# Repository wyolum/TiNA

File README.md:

TiNA
====

Standalone controller for TIM (The Intelligent Matrix)

To install arduino libraries:
1. download and unzip (or git clone) the files to a local directory
   for example, my this is /home/justin/code/TiNA
2. set your arduino sketchbook path to the arduino subdirectory of your install path by either 
    a. editing your ~/.arduino/preferences.txt (the sketchbook.path variable)
    b. selecting from the "File->Preferences" drop down menu item
    for example, my sketchbook path is /home/justin/code/TiNA/arduino
3. start or restart the Arduino IDE

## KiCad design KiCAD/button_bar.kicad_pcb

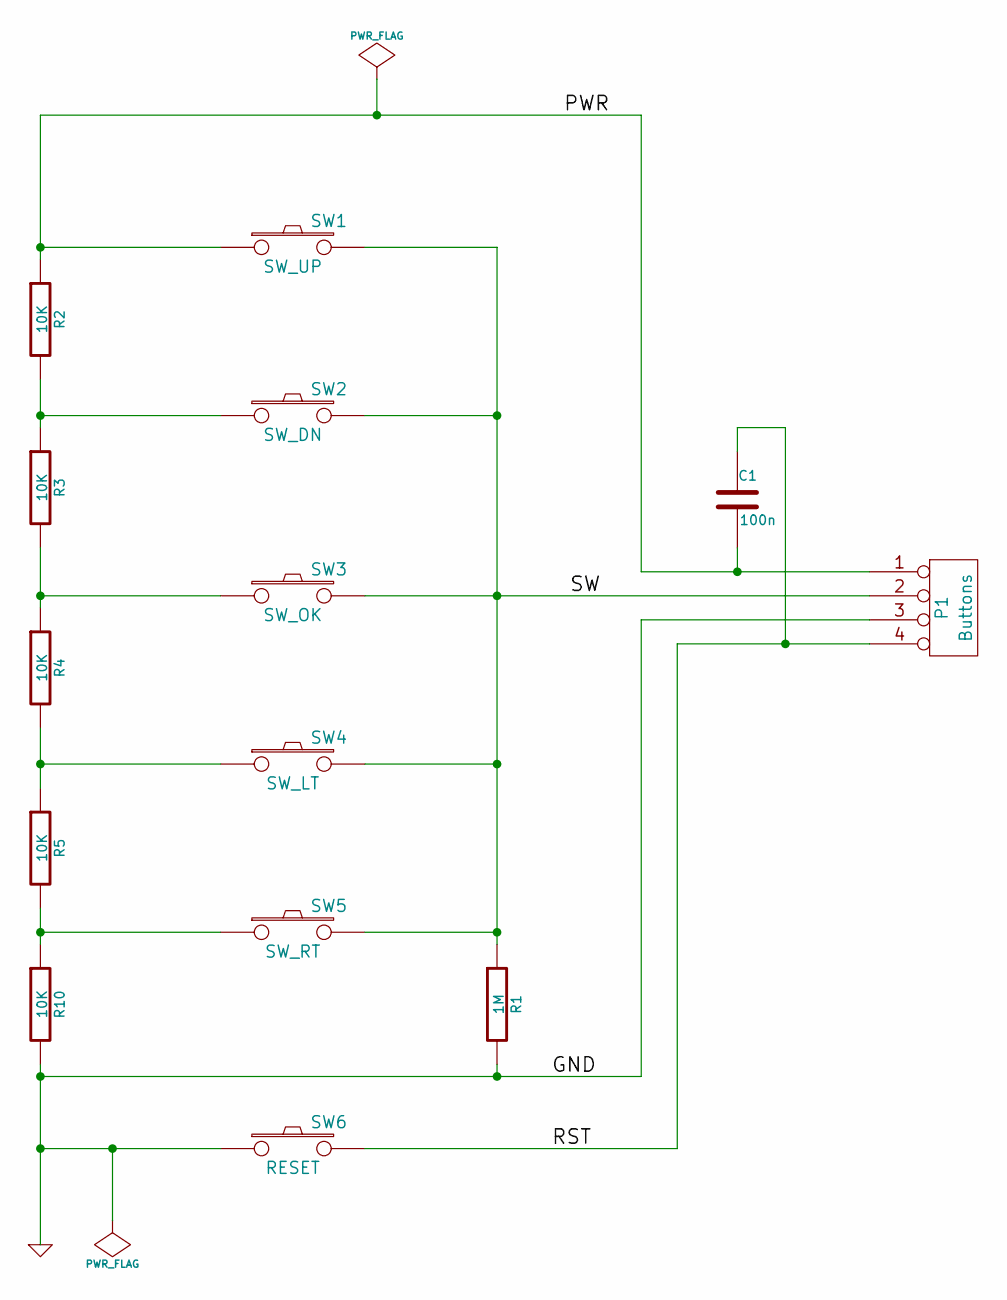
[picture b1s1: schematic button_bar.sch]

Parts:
C1: 100n; C2
P1: Buttons; SIL-4
R1: 1M; RC03
R2, R3, R4, R5, R10: 10K; RC03
SW1: SW_UP; SW-PB
SW2: SW_DN; SW-PB
SW3: SW_OK; SW-PB
SW4: SW_LT; SW-PB
SW5: SW_RT; SW-PB
SW6: RESET; SW-PB

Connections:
/PWR: C1.2, P1.1, R2.1, SW1.1
/RST: C1.1, P1.4, SW6.2
/SW: P1.2, R1.1, SW1.2, SW2.2, SW3.2, SW4.2, SW5.2
GND: P1.3, R1.2, R10.2, SW6.1
unnamed: R5.2, R10.1, SW5.1
unnamed: R4.2, R5.1, SW4.1
unnamed: R3.2, R4.1, SW3.1
unnamed: R2.2, R3.1, SW2.1

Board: 2 copper layers, 14 parts (0 on the bottom side), 8 nets, no tracks yet.

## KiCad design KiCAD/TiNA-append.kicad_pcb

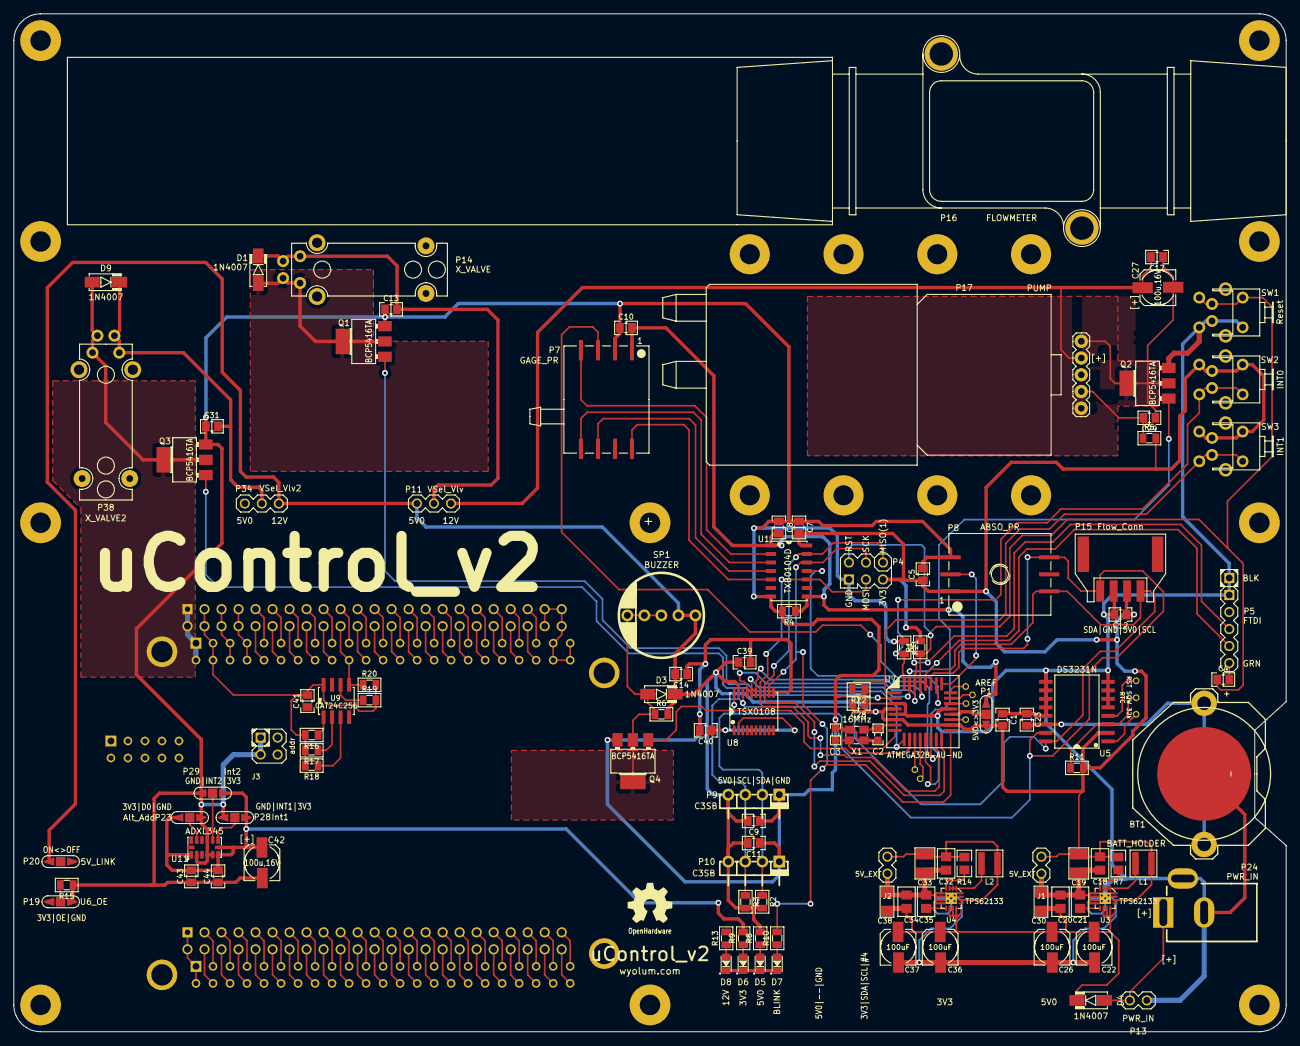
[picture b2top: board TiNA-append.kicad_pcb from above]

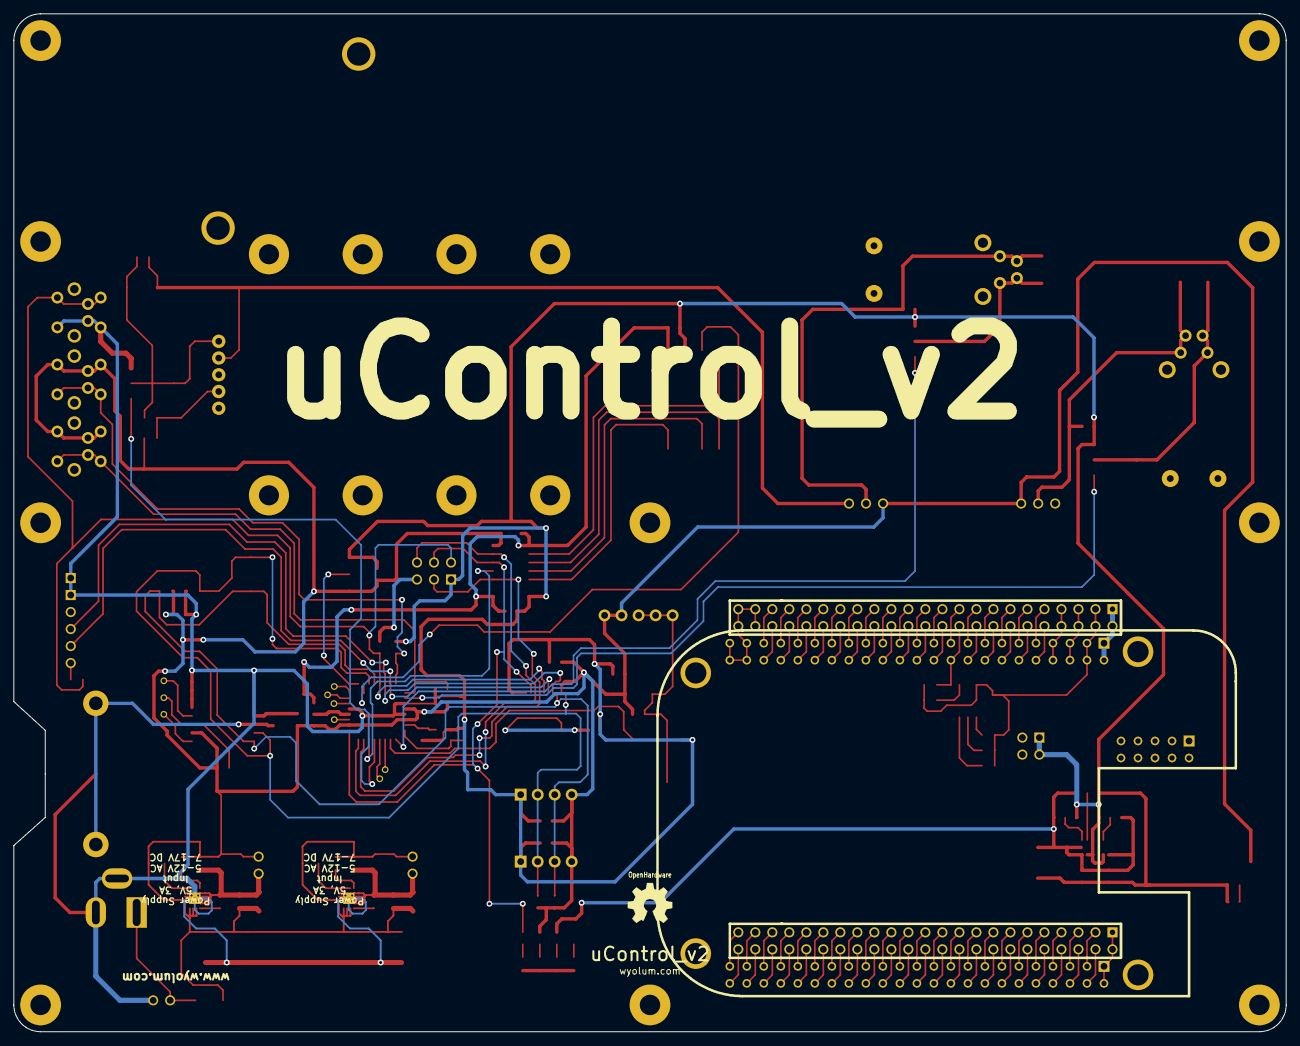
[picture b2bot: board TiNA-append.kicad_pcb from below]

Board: 2 copper layers, 190.0 x 152.0 mm, 137 parts (4 on the bottom side), 147 nets.

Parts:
B1, B2, B3: I_O
B4, B12: PB0; I_O
B8: PC0; I_O
B9: PC1; I_O
B10: PC6; I_O
B11: PC7; I_O
BT1: BATT_HOLDER; CR2032
C1, C4, C5, C7, C8, C9, C10, C11, C12, C13, C14, C17, C23, C28, C29, C31, C39, C40, C41, C43, C44: 100n; c_0805
C2, C3: 22p; c_0603
C18, C20, C32, C34: 100nF; c_0805
C19, C33: 22uF X7R; c_1210
C21, C35: 3.3nF; c_0805
C22, C26, C36, C37: 100uF; C_ELCO_SMD
C27, C42: 100u,16V; C_ELCO_SMD
C30, C38: 10uF X7R; c_1206
D1, D3, D4, D9: 1N4007; diode-DO214AC
D5: 5V0; led_0805
D6: 3V3; led_0805
D7: BLINK; led_0805
D8: 12V; led_0805
G3, G4: Logo_OH; OSHW_6mm
J1, J2: 5V_EXT; Header_2
J3: addr; Header_2x2
L1, L2: 2u2H,3.0A; Inductor_SMD3
P1: AREF; ShortLink2
P4: ICSP; Header_ISP
P5: FTDI; Header_FTDI
P7: GAGE_PR; HCEM500GUH9P3
P8: ABSO_PR; HDIB002AUY8H5
P9, P10: C3SB; pin_strip_4-90
P11: VSel_Vlv; Header_3
P13: PWR_IN; Header_2
P14: X_VALVE; X_Valve_2
P15: Flow_Conn; Conn_Flow_SFM3000_Male
P16: FLOWMETER; FlowMeter_CFM3000
P17: PUMP; Pump_P54E01R_02
P19: U6_OE; ShortLink2
P20: 5V_LINK; ShortLink2
P21, P22: CONN_23X2; PIN_ARRAY_23X2
P23: Alt_Add; ShortLink2
P24: PWR_IN; JACK_ALIM
P28: Int1; ShortLink2
P29: Int2; ShortLink2
P34: VSel_Vlv2; Header_3
P38: X_VALVE2; X_Valve_2
PCB1: PCB
Q1, Q2, Q3, Q4: BCP5416TA; SOT223
R1, R2, R3, R4, R11, R15, R21, R22: 10k; r_0805
R5: 4k7; r_0805
R6, R10, R13: 1k; r_0805
R7, R14: 100k; r_0805
R8: 330E; r_0805
R9: 120E; r_0805
R16, R17, R18: 4k75; r_0805
R19, R20: 1k5; r_0805
SC1, SC2, SC3, SC4, SC5, SC6, SC7, SC8, SC9, SC10: SCREW; vite_3mm
SP1: BUZZER; Speaker
SW1: Reset; SW_PB_V_H
SW2: INT0; SW_PB_V_H
SW3: INT1; SW_PB_V_H
U1: TXB0104D
U3, U4: TPS62133; TPS62132
U5: DS3231N; DS3231
U7: ATMEGA328-AU-ND; TQFP32
U8: TSX0108; TXS0108EPWR
U9: CAT24C256; SO8E
U10: BEAGLEBONE
U11: ADXL345
X1: 16MHz; Xtal_SMD3

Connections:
+3.3V: C8.1, C10.1, C32.2, C33.1, C42.1, C43.1, C44.1, J2.1, L2.2, P1.1, P7.1, P23.3, P28.3, P29.3, R4.2, R9.1, R14.2, U1.1, U1.8, U4.14, U11.1, U11.6, U11.7
/AREF: P1.2, U7.20
/BBB/5V0: C1.1, C5.2, C7.1, C9.1, C11.1, C12.2, C14.1, C18.2, C19.1, C28.1, C39.2, D3.2, J1.1, L1.2, P1.3, P4.2, P8.1, P9.1, P10.1, P11.1, P15.2, P20.1, P34.1, R1.1, R2.1, R3.1, R5.1, R6.1, R7.2, R8.1, R11.1, SP1.1, SW2.2, SW3.2, U1.14, U3.14, U5.2, U7.4, U7.6, U7.18, U8.19
/BBB/A0: J3.3, R16.2, U9.1
/BBB/A1: J3.1, R17.2, U9.2
/BBB/A2: R18.2, U9.3
/BBB/ACL_INT1: P28.2, U11.8
/BBB/ACL_INT2: P29.2, U11.9
/BBB/ACL_SDO: P23.2, U11.12
/BBB/AIN0: P21.39, U10.C39
/BBB/AIN1: P21.40, U10.C40
/BBB/AIN2: P21.37, U10.C37
/BBB/AIN3: P21.38, U10.C38
/BBB/AIN4: P21.33, U10.C33
/BBB/AIN5: P21.36, U10.C36
/BBB/AIN6: P21.35, U10.C35
/BBB/BBB_OE: P19.2, R15.1, U8.10
/BBB/CLKOUT2: P21.41, U10.C41
/BBB/DGND_8: P22.1, P22.2, U10.B1, U10.B2
/BBB/DGND_9_2: P21.43, P21.44, P21.45, P21.46, U10.C43, U10.C44, U10.C45, U10.C46
/BBB/EHRPWM1A: P21.14, U10.C14
/BBB/EHRPWM1B: P21.16, U10.C16
/BBB/EHRPWM2A: P22.19, U10.B19
/BBB/EHRPWM2B: P22.13, U10.B13
/BBB/GNDA_ADC: P21.34, U10.C34
/BBB/GPIO0_7: P21.42, U10.C42
/BBB/GPIO0_26: P22.14, U10.B14
/BBB/GPIO0_27: P22.17, U10.B17
/BBB/GPIO1_0: P22.25, U10.B25
/BBB/GPIO1_1: P22.24, U10.B24
/BBB/GPIO1_2: P22.5, U10.B5
/BBB/GPIO1_3: P22.6, U10.B6
/BBB/GPIO1_4: P22.23, U10.B23
/BBB/GPIO1_5: P22.22, U10.B22
/BBB/GPIO1_6: P22.3, U10.B3
/BBB/GPIO1_7: P22.4, U10.B4
/BBB/GPIO1_12: P22.12, U10.B12
/BBB/GPIO1_13: P22.11, U10.B11
/BBB/GPIO1_14: P22.16, U10.B16
/BBB/GPIO1_15: P22.15, U10.B15
/BBB/GPIO1_16: P21.15, U10.C15
/BBB/GPIO1_17: P21.23, U10.C23
/BBB/GPIO1_28: P21.12, U10.C12
/BBB/GPIO1_29: P22.26, U10.B26
/BBB/GPIO1_30: P22.21, U10.B21
/BBB/GPIO1_31: P22.20, U10.B20
/BBB/GPIO2_1: P22.18, U10.B18
/BBB/GPIO2_6: P22.45, U10.B45
/BBB/GPIO2_7: P22.46, U10.B46
/BBB/GPIO2_8: P22.43, U10.B43
/BBB/GPIO2_9: P22.44, U10.B44
/BBB/GPIO2_10: P22.41, U10.B41
/BBB/GPIO2_11: P22.42, U10.B42
/BBB/GPIO2_13: P22.40, U10.B40
/BBB/GPIO2_22: P22.27, U10.B27
/BBB/GPIO2_23: P22.29, U10.B29
/BBB/GPIO2_24: P22.28, U10.B28
/BBB/GPIO2_25: P22.30, U10.B30
/BBB/GPIO3_19: P21.27, U10.C27
/BBB/GPIO3_21: P21.25, U10.C25
/BBB/GPIO_12: P22.39, U10.B39
/BBB/I2C1_SCL: P21.17, U8.3, U10.C17, U11.14
/BBB/I2C1_SDA: P21.18, U8.1, U10.C18, U11.13
/BBB/I2C2_SCL: P21.19, R19.2, U9.6, U10.C19
/BBB/I2C2_SDA: P21.20, R20.2, U9.5, U10.C20
/BBB/MISO: P4.1, U1.13, U7.16, U8.13
/BBB/PWR_BUT: P21.9, U10.C9
/BBB/RESET: C4.2, P4.5, R1.2, SW1.2, U7.29, U8.15
/BBB/RXD: P5.4, U7.30, U8.17
/BBB/SCK: P4.3, R10.1, U1.12, U7.17, U8.12
/BBB/SCL: P8.6, P9.2, P10.2, P15.1, R3.2, U5.16, U7.28, U8.18
/BBB/SDA: P8.4, P9.3, P10.3, P15.4, R2.2, U5.15, U7.27, U8.20
/BBB/SPI1_CS0: P21.28, U10.C28
/BBB/SPI1_D0: P21.29, U8.8, U10.C29
/BBB/SPI1_D1: P21.30, U8.7, U10.C30
/BBB/SPI1_SCLK: P21.31, U8.9, U10.C31
/BBB/SYS_5V: P21.7, P21.8, U10.C7, U10.C8
/BBB/SYS_RESETn: P21.10, U10.C10
/BBB/TIMER4: P22.7, U10.B7
/BBB/TIMER5: P22.9, U10.B9
/BBB/TIMER6: P22.10, U10.B10
/BBB/TIMER7: P22.8, U10.B8
/BBB/TXD: P5.5, U7.31, U8.16
/BBB/UART1_RXD: P21.26, U8.5, U10.C26
/BBB/UART1_TXD: P21.24, U8.4, U10.C24
/BBB/UART2_RXD: P21.22, U10.C22
/BBB/UART2_TXD: P21.21, U10.C21
/BBB/UART3_CTSN: P22.36, U10.B36
/BBB/UART3_RTSN: P22.34, U10.B34
/BBB/UART4_CTSN: P22.35, U10.B35
/BBB/UART4_RTSN: P22.33, U10.B33
/BBB/UART4_RXD: P21.11, U10.C11
/BBB/UART4_TXD: P21.13, U10.C13
/BBB/UART5_CTSN: P22.31, U10.B31
/BBB/UART5_RTSN: P22.32, U10.B32
/BBB/UART5_RXD: P22.38, U10.B38
/BBB/UART5_TXD: P22.37, U10.B37
/BBB/VDD_3V3EXP: C40.2, C41.1, P19.1, P21.3, P21.4, R16.1, R17.1, R18.1, R19.1, R20.1, U8.2, U9.8, U10.C3, U10.C4
/BBB/VDD_5V: P20.2, P21.5, P21.6, U10.C5, U10.C6
/BBB/VDD_ADC: P21.32, U10.C32
/BBB/~MOSI: P4.4, U1.10, U7.15, U8.14
/Interface/12V: C17.1, C20.2, C22.1, C26.1, C27.1, C30.1, C34.2, C36.1, C37.1, C38.1, D4.2, P11.3, P17.2, P34.3, R13.1, U3.10, U3.11, U3.12, U3.13, U4.10, U4.11, U4.12, U4.13
/Interface/+Vlv: C13.1, D1.2, P11.2, P14.1
/Interface/+Vlv2: C31.1, D9.2, P34.2, P38.1
/Interface/-Vlv: D1.1, P14.2, Q1.2
/Interface/-Vlv2: D9.1, P38.2, Q3.2
/Interface/PC2_Pr2: P8.2, U7.25
/Interface/PC3_Pr1: P7.3, U7.26
/Interface/PD4_Valve2: Q3.1, U7.2
/Interface/P_MISO: P7.4, U1.2
/Interface/P_MOSI: P7.8, U1.5
/Interface/P_SCK: P7.5, U1.3
/Interface/P_SS: P7.6, U1.4
/Interface/Pump: C29.1, P17.4, R5.2
/Interface/Spk: D3.1, Q4.2, R6.2, SP1.2
/Interface/~PB1_Pump: Q2.1, U7.13
/Interface/~PD5_Valve: Q1.1, U7.9
/Interface/~PD6_Spk: Q4.1, U7.10
/Interface/~SS: U1.11, U7.14
/PB0: B12.1, U7.12
/PB6: C2.1, U7.7, X1.1
/PB7: C3.1, U7.8, X1.2
/PC0: B8.1, U7.23
/PC1: B9.1, U7.24
/PC6: B10.1, U7.19
/PC7: B11.1, U7.22
/PD2: R21.1, SW2.1, U7.32
/PD7: B4.1, U7.11
/pwr/PWR_IN: D4.1, P13.1, P24.1
/rtc/32k: B3.1, U5.1
/rtc/BAT: BT1.+, C23.1, U5.14
/rtc/RST: B2.1, U5.4
/rtc/SQR: B1.1, R11.2, U5.3
/~PD3: R22.1, SW3.1, U7.1
/~RTS: C4.1, P5.6
GND: BT1.-, C1.2, C2.2, C3.2, C5.1, C7.2, C8.2, C9.2, C10.2, C11.2, C12.1, C13.2, C14.2, C18.1, C19.2, C20.1, C21.1, C22.2, C23.2, C26.2, C28.2, C30.2, C31.2, C32.1, C33.2, C34.1, C35.1, C36.2, C37.2, C38.2, C39.1, C40.1, C41.2, C42.2, C43.2, C44.2, D5.2, D6.2, D7.2, D8.2, J1.2, J2.2, J3.2, J3.4, P4.6, P5.1, P5.2, P7.2, P8.3, P9.4, P10.4, P13.2, P15.3, P19.3, P21.1, P21.2, P23.1, P24.2, P24.3, P28.1, P29.1, Q1.3, Q2.3, Q3.3, Q4.3, R4.1, R15.2, R21.2, R22.2, SW1.1, U1.7, U3.5, U3.6, U3.7, U3.8, U3.15, U3.16, U4.5, U4.6, U4.7, U4.8, U4.15, U4.16, U5.5, U5.6, U5.7, U5.8, U5.9, U5.10, U5.11, U5.12, U5.13, U7.3, U7.5, U7.21, U8.11, U9.4, U10.C1, U10.C2, U11.2, U11.4, U11.5, U11.10, X1.3
unnamed: C21.2, U3.9
unnamed: L1.1, U3.1, U3.2, U3.3
unnamed: R7.1, U3.4
unnamed: D7.1, R10.2
unnamed: D8.1, R13.2
unnamed: D6.1, R9.2
unnamed: D5.1, R8.2
unnamed: C35.2, U4.9
unnamed: L2.1, U4.1, U4.2, U4.3
unnamed: R14.1, U4.4
unnamed: C17.2, C27.2, C29.2, P17.1, Q2.2

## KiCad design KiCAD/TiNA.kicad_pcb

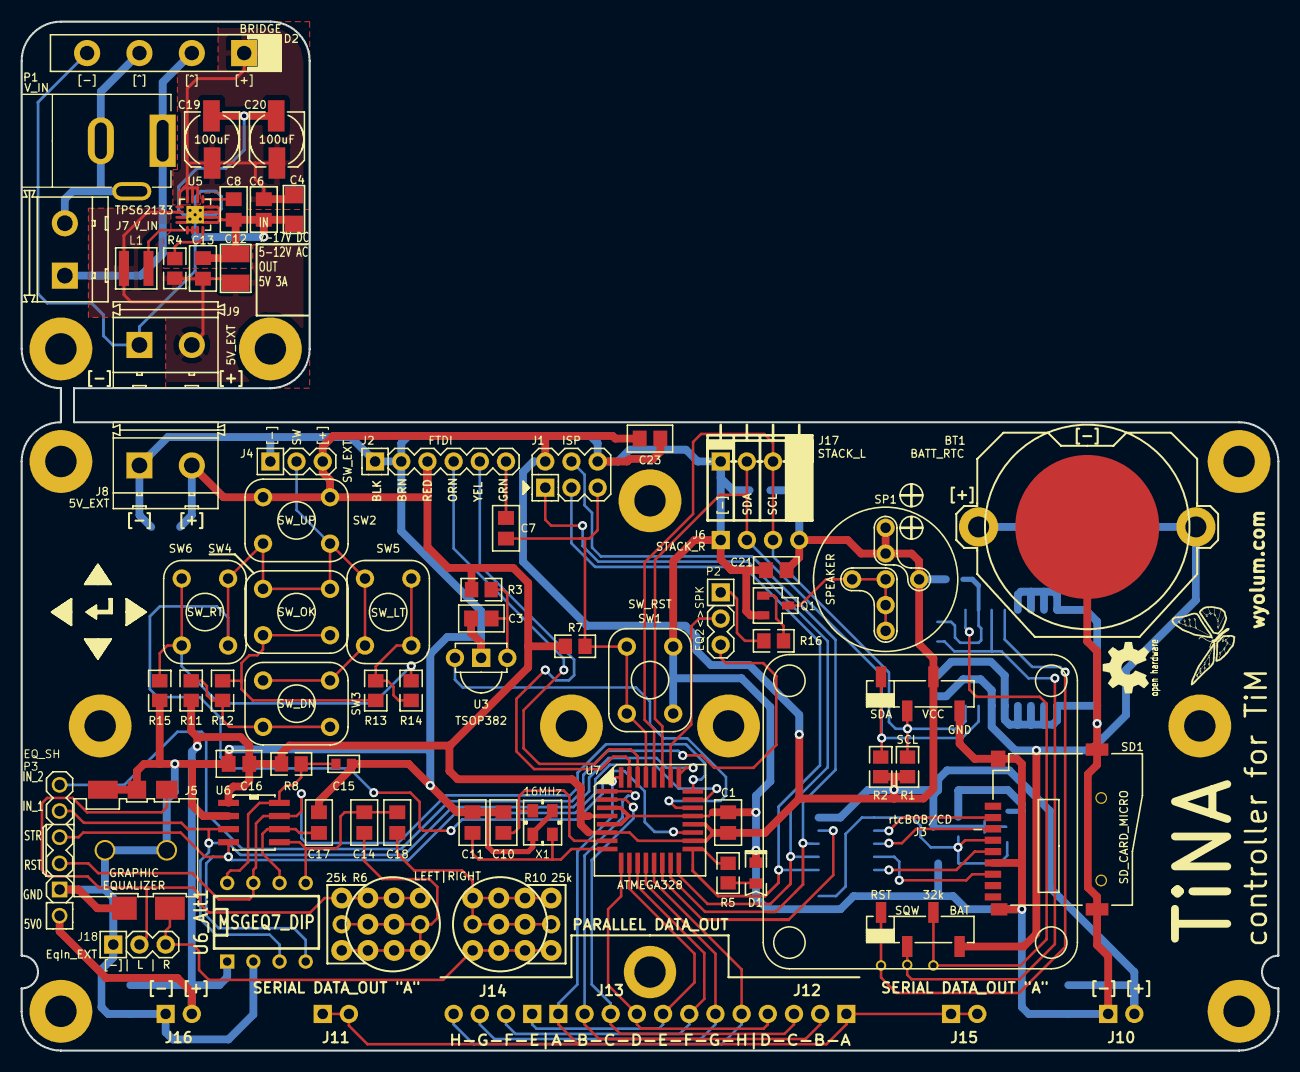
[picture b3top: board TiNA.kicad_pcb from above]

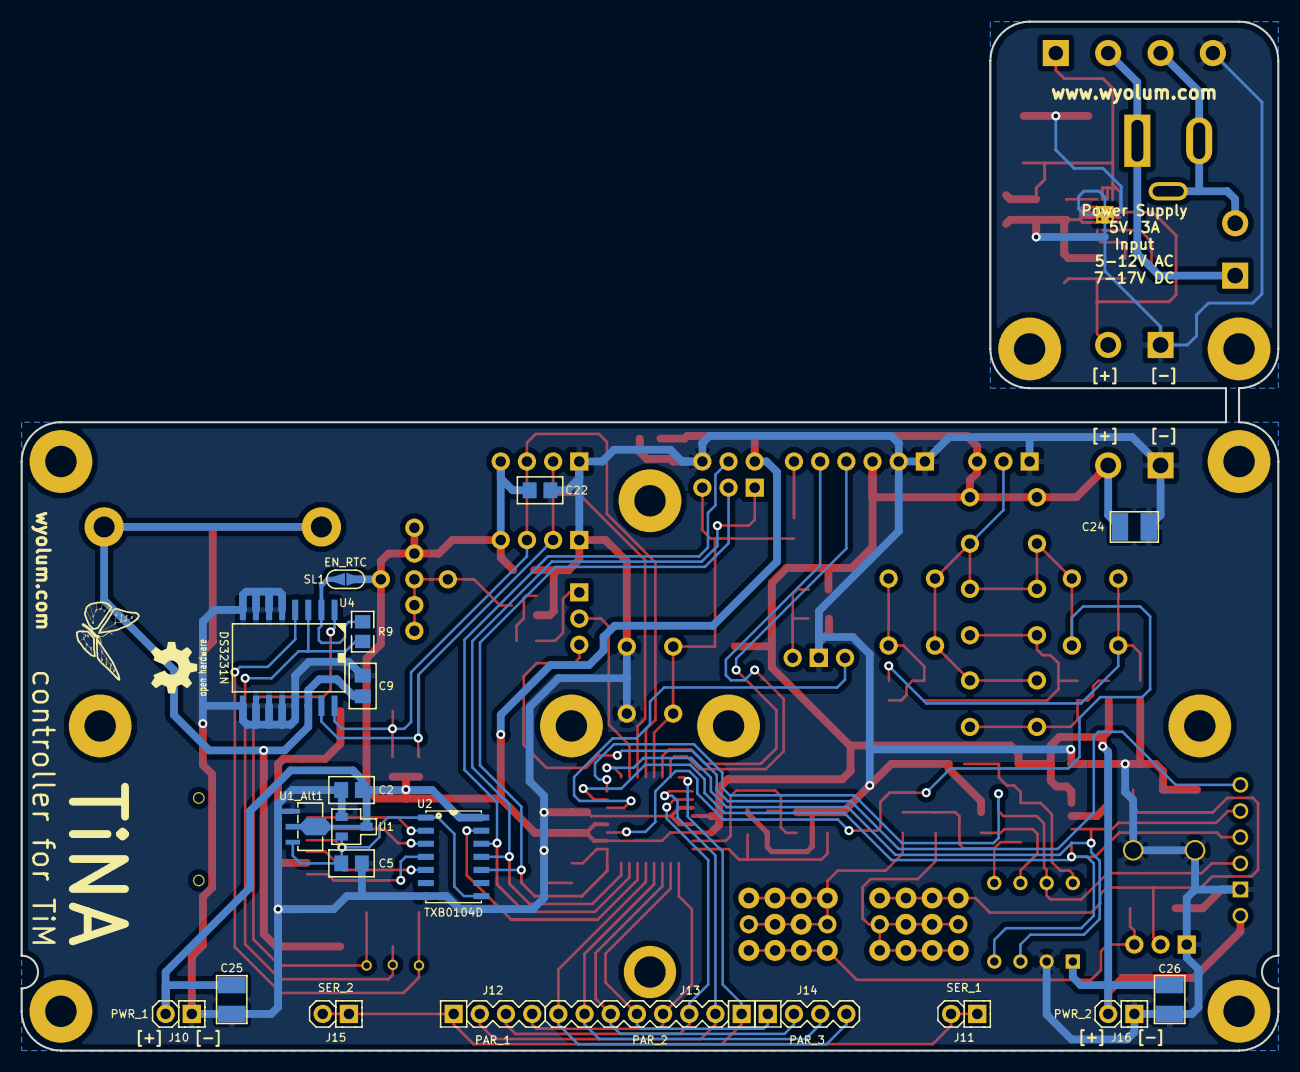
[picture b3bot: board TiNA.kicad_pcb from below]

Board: 2 copper layers, 121.9 x 99.8 mm, 104 parts (21 on the bottom side), 63 nets.

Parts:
B2, B3, B15: I/O; O%3a
BT1: BATT_RTC; CR2032
C1, C6, C7, C9, C13, C16, C17, C21, C22, C23: 100nF; c_0805
C2, C5: 1uF; c_0805
C3: 220nF; c_0805
C4: 10uF X7R; c_1206
C8: 3.3nF; c_0805
C10, C11: 22pF; c_0805
C12, C24, C25, C26: 22uF X7R; c_1210
C14, C18: 10nF; c_0805
C15: 33pF; c_0603
C19, C20: 100uF; C_ELCO_SMD
D1: LED; d_0805
D2: BRIDGE; Bridge
G1, G1#2: Logo-WL3
J1: ISP
J2: FTDI; PIN_ARRAY-6X1
J3: rtcBOB/CD; rtcBOB
J4: SW_EXT; PIN_ARRAY_3x1
J5: JACK_3.5MM_5PIN; Jack_3.5mm_SJ1-3513
J6: STACK_L; STACK-L
J7: V_IN; bornier2
J8, J9: 5V_EXT; bornier2
J10: PWR_1; pin_strip_2
J11: SER_1; pin_strip_2
J12: PAR_1; PIN_ARRAY_4x1
J13: PAR_2; SIL-8
J14: PAR_3; PIN_ARRAY_4x1
J15: SER_2; pin_strip_2
J16: PWR_2; pin_strip_2
J17: STACK_R; STACK-R
J18: EqIn_EXT; PIN_ARRAY_3x1
L1: 2u2H,3.0A; Inductor_SMD3
P1: V_IN; JACK_ALIM
P2: EQ2<>SPK; PIN_ARRAY_3x1
P3: EQ_SH; PIN_ARRAY-6X1
Q1: MMBT2222; SOT23-3-NPN
R1, R2, R7, R9, R11, R12, R13, R14, R15: 10k; r_0805
R3: 100E; r_0805
R4: 100k; r_0805
R5, R16: 1k5; r_0805
R6, R10: 25k; Pot-Var2
R8: 200k; r_0805
SC1, SC2, SC3, SC4, SC5, SC6, SC7, SC8, SC9, SC10, SC11, SC12: SCREW; vite_3mm
SD1: SD_CARD_MICRO; SD_Micro_seeed
SL1: EN_RTC; ShortLink
SP1: SPEAKER; Speaker_2
SW1: SW_RST; SW-PB
SW2: SW_UP; SW-PB
SW3: SW_DN; SW-PB
SW4: SW_OK; SW-PB
SW5: SW_LT; SW-PB
SW6: SW_RT; SW-PB
U1: MCP1700T-3V3 SOT23-3; SOT23-3
U1_Alt1: MCP1700T-3V3 SOT89; SOT89
U2: TXB0104D
U3: TSOP382
U4: DS3231N; DS3231
U5: TPS62133; TPS62132
U6: MSGEQ7; SO8E
U6_Alt1: MSGEQ7_DIP; DIP-8__300
U7: ATMEGA328; TQFP32
X1: 16MHz; Xtal_SMD3

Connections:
+3.3V: C5.1, SD1.4, U1.2, U1_Alt1.3, U2.1, U2.8
/5V_Out: C12.1, C13.2, J9.1, L1.2, R4.2, U5.14
/AC1: D2.2, J7.2, P1.1
/AC2: D2.3, J7.1, P1.2, P1.3
/EQ_CG: C17.2, U6.6, U6_Alt1.6
/EQ_IN: C14.1, C18.1, U6.5, U6_Alt1.5
/EQ_IN_L: J5.3, J18.2, R6.1
/EQ_IN_R: J5.2, J18.3, R10.1
/EQ_OSC: C15.1, R8.1, U6.8, U6_Alt1.8
/EQ_OUT1: P3.5, U6.3, U6_Alt1.3, U7.25
/EQ_OUT2: P2.3, P3.6
/EQ_RST: P3.3, U6.7, U6_Alt1.7, U7.24
/EQ_STR: P3.4, U6.4, U6_Alt1.4, U7.23
/GND_PWR: C4.2, C6.1, C8.1, C12.2, C13.1, C19.2, C20.2, D2.4, J9.2, U5.5, U5.6, U5.7, U5.8, U5.15, U5.16
/Ir_Dat: U3.1, U7.22
/MISO: J1.1, U2.11, U7.16
/MOSI: J1.4, U2.12, U7.15
/OPTION: P2.2, U7.26
/PB6: C10.1, U7.7, X1.1
/PB7: C11.1, U7.8, X1.2
/PWR_IN: C4.1, C6.2, C19.1, C20.1, D2.1, U5.10, U5.11, U5.12, U5.13
/RESET: C7.2, J1.5, R7.2, SW1.2, U7.29
/RXD: J2.4, U7.30
/RowA: J11.1, J11.2, J12.1, J13.1, J15.1, J15.2, U7.32
/RowB: J12.2, J13.2, U7.1
/RowC: J12.3, J13.3, U7.2
/RowD: J12.4, J13.4, U7.9
/RowE: J13.5, J14.1, U7.10
/RowF: J13.6, J14.2, U7.11
/RowG: J13.7, J14.3, U7.12
/RowH: J13.8, J14.4, U7.13
/SCK: J1.3, R5.1, U2.10, U7.17
/SD_CLK: SD1.5, U2.5
/SD_CS: SD1.2, U2.2
/SD_DATA_IN: SD1.3, U2.3
/SD_DATA_OUT: SD1.7, U2.4
/SPK: P2.1, R16.1
/SS: U2.13, U7.14
/SW: J4.2, SW2.2, SW3.2, SW4.2, SW5.2, SW6.2, U7.19
/TXD: J2.5, U7.31
/TiNA_rtc/5V0: C1.1, C2.1, C16.2, C21.2, C22.2, C23.2, C24.1, C25.1, C26.1, J1.2, J2.3, J3.7, J4.3, J6.1, J8.1, J10.1, J16.1, J17.1, P3.1, R1.1, R2.1, R3.1, R7.1, R8.2, R11.2, SL1.2, SP1.1, SW2.1, U1.3, U1_Alt1.2, U2.14, U6.1, U6_Alt1.1, U7.4, U7.6, U7.18, U7.20
/TiNA_rtc/32k: B15.1, J3.3, U4.1
/TiNA_rtc/BAT: BT1.+, C9.1, J3.4, U4.14
/TiNA_rtc/RST: B3.1, J3.1, U4.4
/TiNA_rtc/SCL: J3.6, J6.2, J17.2, R1.2, U4.16, U7.28
/TiNA_rtc/SDA: J3.5, J6.3, J17.3, R2.2, U4.15, U7.27
/TiNA_rtc/SQW: B2.1, J3.2, R9.2, U4.3
GND: BT1.-, C1.2, C2.2, C3.1, C5.2, C9.2, C10.2, C11.2, C15.2, C16.1, C17.1, C21.1, C22.1, C23.1, C24.2, C25.2, C26.2, D1.2, J1.6, J2.1, J2.2, J3.8, J4.1, J5.1, J5.4, J5.5, J6.4, J8.2, J10.2, J16.2, J17.4, J18.1, P3.2, Q1.1, R15.1, SD1.6, SD1.G1, SD1.G2, SD1.G3, SD1.G4, SW1.1, U1.1, U1_Alt1.1, U2.7, U3.2, U4.5, U4.6, U4.7, U4.8, U4.9, U4.10, U4.11, U4.12, U4.13, U6.2, U6_Alt1.2, U7.3, U7.5, U7.21, X1.3
unnamed: C3.2, R3.2, U3.3
unnamed: C7.1, J2.6
unnamed: C8.2, U5.9
unnamed: C14.2, R6.2, R6.3
unnamed: C18.2, R10.2, R10.3
unnamed: D1.1, R5.2
unnamed: L1.1, U5.1, U5.2, U5.3
unnamed: Q1.2, R16.2
unnamed: Q1.3, SP1.2
unnamed: R4.1, U5.4
unnamed: R9.1, SL1.1, U4.2
unnamed: R11.1, R12.2, SW3.1
unnamed: R12.1, R13.2, SW4.1
unnamed: R13.1, R14.2, SW5.1
unnamed: R14.1, R15.2, SW6.1

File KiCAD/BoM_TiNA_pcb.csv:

"Id";"Designator";"Package";"Quantity";"Designation";"Supplier and ref";
1;"D2";"Bridge";1;"BRIDGE";;;
2;"R4";"r_0805";1;"100k";;;
3;"P1";"JACK_ALIM";1;"V_IN";;;
4;"C20,C19";"C_ELCO_SMD";2;"100uF";;;
5;"C6,C13,C1,C7,C9,C17,C16,C21,C22,C23";"c_0805";10;"100nF";;;
6;"C8";"c_0805";1;"3.3nF";;;
7;"U5";"TPS62132";1;"TPS62133";;;
8;"J3";"rtcBOB";1;"rtcBOB/CD";;;
9;"C2,C5";"c_0805";2;"1uF";;;
10;"C3";"c_0805";1;"220nF";;;
11;"C10,C11";"c_0805";2;"22pF";;;
12;"C14,C18";"c_0805";2;"10nF";;;
13;"J17";"STACK-R";1;"STACK_R";;;
14;"R6,R10";"Pot-Var2";2;"25k";;;
15;"J2";"PIN_ARRAY-6X1";1;"FTDI";;;
16;"J12";"PIN_ARRAY_4x1";1;"PAR_1";;;
17;"J14";"PIN_ARRAY_4x1";1;"PAR_3";;;
18;"BT1";"CR2032";1;"BATT_RTC";;;
19;"R8";"r_0805";1;"200k";;;
20;"U6";"SO8E";1;"MSGEQ7";;;
21;"R3";"r_0805";1;"100E";;;
22;"X1";"Xtal_SMD2";1;"16MHz";;;
23;"U4";"DS3231";1;"DS3231N";;;
24;"U2";"TXB0104D";1;"TXB0104D";;;
25;"R9,R7,R2,R1,R11,R12,R13,R14,R15";"r_0805";9;"10k";;;
26;"R5,R16";"r_0805";2;"1k5";;;
27;"U7";"TQFP32";1;"ATMEGA328";;;
28;"B15,B3,B2";"I/O";3;"I/O";;;
29;"J13";"SIL-8";1;"PAR_2";;;
30;"J1";"ISP";1;"ISP";;;
31;"Q1";"SOT23-3";1;"MMBT2222";;;
32;"U1";"SOT23-3";1;"MCP1700T-3V3 SOT23-3";;;
33;"D1";"d_0805";1;"LED";;;
34;"U3";"TSOP382";1;"TSOP382";;;
35;"J5";"Jack_3.5mm_SJ1-3513";1;"JACK_3.5MM_5PIN";;;
36;"SW1";"SW-PB";1;"SW_RST";;;
37;"SW2";"SW-PB";1;"SW_UP";;;
38;"SW3";"SW-PB";1;"SW_DN";;;
39;"SW4";"SW-PB";1;"SW_OK";;;
40;"SW5";"SW-PB";1;"SW_LT";;;
41;"SW6";"SW-PB";1;"SW_RT";;;
42;"SC9,SC6,SC7,SC5,SC8,SC2,SC3,SC1,SC4,SC12,SC11,SC10";"vite_3mm";12;"SCREW";;;
43;"J4";"PIN_ARRAY_3x1";1;"SW_EXT";;;
44;"J8,J9";"bornier2";2;"5V_EXT";;;
45;"J7";"bornier2";1;"V_IN";;;
46;"J6";"STACK-L";1;"STACK_L";;;
47;"J15";"pin_strip_2";1;"SER_2";;;
48;"J16";"pin_strip_2";1;"PWR_2";;;
49;"J11";"pin_strip_2";1;"SER_1";;;
50;"J10";"pin_strip_2";1;"PWR_1";;;
51;"SD1";"SD_Micro_seeed";1;"SD_CARD_MICRO";;;
52;"J18";"PIN_ARRAY_3x1";1;"EqIn_EXT";;;
53;"C15";"c_0603";1;"33pF";;;
54;"SP1";"Speaker_2";1;"SPEAKER";;;
55;"C12,C24,C26,C25";"c_1210";4;"22uF X7R";;;
56;"C4";"c_1206";1;"10uF X7R";;;
57;"L1";"Inductor_SMD3";1;"2u2H,3.0A";;;
58;"U6_Alt1";"DIP-8__300";1;"MSGEQ7_DIP";;;
59;"U1_Alt1";"SOT89";1;"MCP1700T-3V3 SOT89";;;
60;"P2";"PIN_ARRAY_3x1";1;"SPK<>EQ2";;;
61;"P3";"PIN_ARRAY-6X1";1;"EQ_SH";;;

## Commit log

2014-01-30 Add test programs and useful libraries
2014-01-31 forgot to init the MSGEq7
2014-02-07 change pinMode for old style compatibility
2014-02-07 modified buttonTest for new 1M Ohm pull down on SW
2014-02-11 added examples and clock and TiNA library
2014-02-11 made bitmap buffers for r/g/b to avoid SD use in Clock.ino
2014-02-12 equalizer example
2014-02-12 removed redundant libraries
2014-02-13 clock.ino works with time set functions and brigtness settings
2014-02-13 Clock.ino now supports time sync to the second.
2014-02-15 minimal working 4 TiM clock
2014-02-15 added a fabrication directory and files
2014-02-15 added tabs to prevent roll up
2014-02-17 made edge piece for cornercube.scad
2014-02-17 added Serial interface to Clock.ino example
2014-02-19 started button interface. added python serial interface
2014-02-19 setter.py now functions as a remote interface
2014-02-21 merged Anool's mods
2014-02-21 move filter cap to connect to ground
2014-02-21 added tracks, moved to new directory
2014-02-21 redo tracks
2014-02-21 finished tracks on ButtonBar
2014-02-21 switched PMU to TinyGPS++
2014-02-21 got PTU working agian with TinyGPS++
2014-02-21 button board pcb update ajm
2014-02-21 fixed PTU.pde
2014-02-27 working on PTU glitches
2014-03-03 start up in dim mode to save batteries
2014-03-03 added button box laser cut drawing
2014-03-04 squared reset button bar
2014-03-04 cleaned up setter.py
2014-03-08 minor gui mods
2014-05-17 I added a couple of colors and changed the countdown time earlier today. just copied that one over to the TiNA folder
2014-09-26 added KiCad design files for TiNA
